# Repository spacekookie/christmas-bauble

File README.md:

# Kookies Christmas Bauble
A jolly christmas decoration on a PCB. Hoo hoo hoo!

It uses a 555 timer and a shift register + two buttons to generate patterns that are then displayed on a ring of simple LED's on the outside. The perfect thing to hang off your christmas tree in the jolly season (I know I'm early...) :)

The design uses SMD components (except for the LED's that are throughhole). The original schematic and layout was done by Ashley Mills (https://github.com/staropram). **The board requires only one layer**! It can thus be made at home (if the apropriate tools for cutting the PCB are present).

Check out my blog article [here](http://spacekookie.de/hardware/jolly-christmas-decoration/) for details :)
The christmas bauble went into production on 17.11.2015. Unfortunately Revision 3.1 got produced, not the updated and much cooler Rev 3.2** :/ Check out the picture belo.wspi

**All the revision 3 boards up to and including Rev 3.2 have a flaw where the XOR gate (U1) will make the functionality useless!**
Do not solder it on. You have to bridge two pins to make it work. Revision 3.3 fixes the issue.

## Pictures

## Partlist

Battery Holder: http://www.mouser.de/ProductDetail/Keystone-Electronics/3012TR/?qs=sGAEpiMZZMtT9MhkajLHrixYIYDZwOfD%2fKquWGKQDng%3d

Resistors: http://www.mouser.de/Passive-Components/Resistors/SMD-Resistors-Chip-Resistors/_/N-7h7yu?P=1yzmno7Z1yzmotu

595 Shift register: http://www.mouser.de/ProductDetail/Texas-Instruments/SN74HC165DR/?qs=sGAEpiMZZMtYFXwiBRPs00UWwMKcYyCs

555 Timer: http://www.mouser.de/ProductDetail/Texas-Instruments/TLC555CDR/?qs=sGAEpiMZZMuHTYi1bHPYELMHAyKcqQNZ

Capacitor: http://www.mouser.de/ProductDetail/Murata-Electronics/GRM32ER71E226KE15L/?qs=sGAEpiMZZMs0AnBnWHyRQAqZuYDIKiCDcXG6%252bp%252b0hpI%3d (you want 22 µF - Not sure if that's included in the Schematic and I'm too lazy to check right now)

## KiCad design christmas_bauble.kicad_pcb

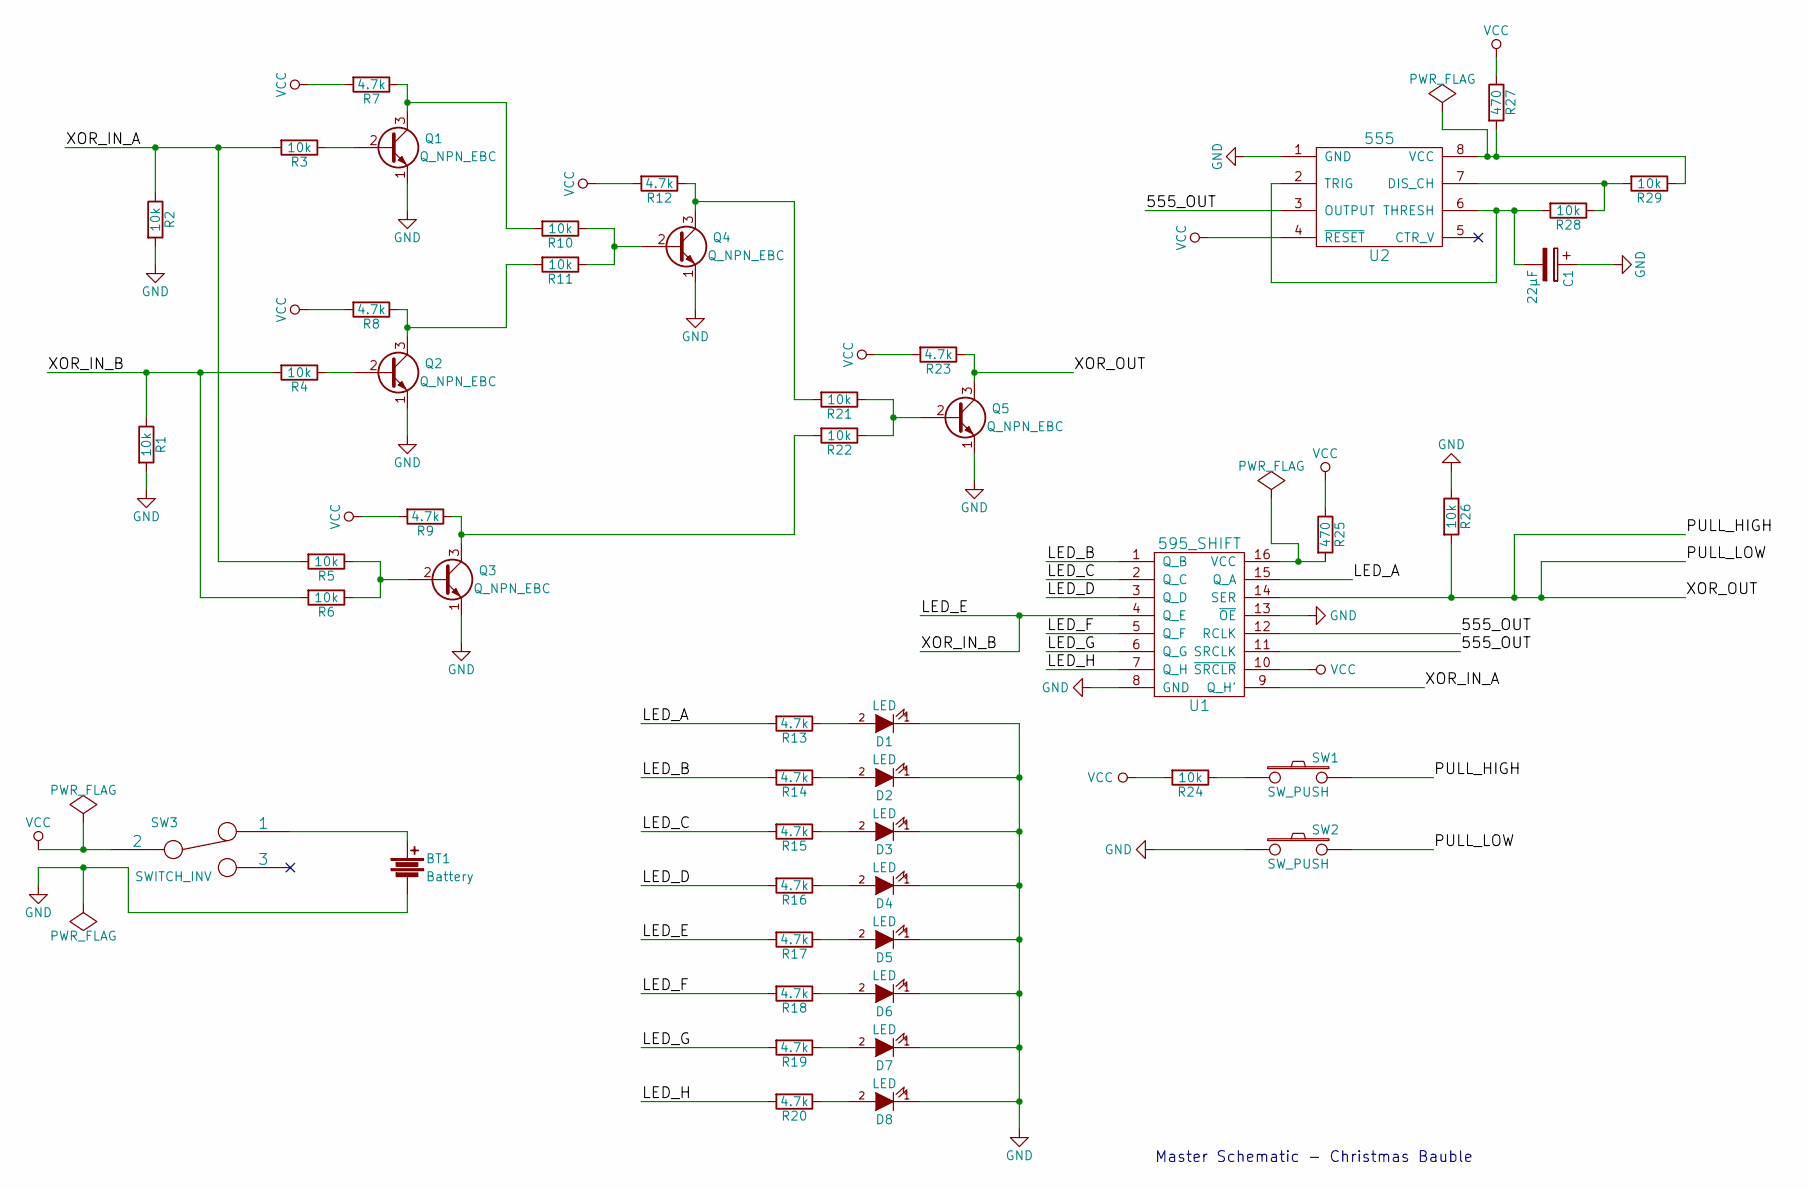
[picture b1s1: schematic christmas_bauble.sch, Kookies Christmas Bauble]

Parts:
BT1: Battery; COIN_BAT_HOLDER
C1: 22µF; C_2225_HandSoldering
D1, D2, D3, D4, D5, D6, D7, D8: LED; LED-5MM
Q1, Q2, Q3, Q4, Q5: Q_NPN_EBC; SOT-23_Handsoldering
R1, R2, R3, R4, R5, R6, R10, R11, R21, R22, R24, R26, R28, R29: 10k; R_1210_HandSoldering
R7, R8, R9, R12, R13, R14, R15, R16, R17, R18, R19, R20, R23: 4.7k; R_1210_HandSoldering
R25, R27: 470; R_1210_HandSoldering
SW1, SW2: SW_PUSH; SW_TACTILE_SHALLOW
SW3: SWITCH_INV; C1-1
U1: 595_SHIFT; SO-16-N
U2: 555; DIP-8_SMD

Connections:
/555_OUT: U1.11 (SRCLK), U1.12 (RCLK), U2.3 (OUTPUT)
/LED_A: R13.2, U1.15 (Q_A)
/LED_B: R14.2, U1.1 (Q_B)
/LED_C: R15.2, U1.2 (Q_C)
/LED_D: R16.2, U1.3 (Q_D)
/LED_E: R1.1, R4.2, R6.2, R17.2, U1.4 (Q_E)
/LED_F: R18.2, U1.5 (Q_F)
/LED_G: R19.2, U1.6 (Q_G)
/LED_H: R20.2, U1.7 (Q_H)
/PULL_HIGH: Q5.3 (C), R23.1, R26.2, SW1.2, SW2.2, U1.14 (SER)
/XOR_IN_A: R2.1, R3.2, R5.2, U1.9 (Q_H')
GND: BT1.2, C1.1, D1.1 (K), D2.1 (K), D3.1 (K), D4.1 (K), D5.1 (K), D6.1 (K), D7.1 (K), D8.1 (K), Q1.1 (E), Q2.1 (E), Q3.1 (E), Q4.1 (E), Q5.1 (E), R1.2, R2.2, R26.1, SW2.1, U1.8 (GND), U1.13 (~OE), U2.1 (GND)
unnamed: BT1.1, SW3.1
unnamed: C1.2, R28.2, U2.2 (TRIG), U2.6 (THRESH)
unnamed: D1.2 (A), R13.1
unnamed: D2.2 (A), R14.1
unnamed: D3.2 (A), R15.1
unnamed: D4.2 (A), R16.1
unnamed: D5.2 (A), R17.1
unnamed: D6.2 (A), R18.1
unnamed: D7.2 (A), R19.1
unnamed: D8.2 (A), R20.1
unnamed: Q1.2 (B), R3.1
unnamed: Q1.3 (C), R7.1, R10.2
unnamed: Q2.2 (B), R4.1
unnamed: Q2.3 (C), R8.1, R11.2
unnamed: Q3.2 (B), R5.1, R6.1
unnamed: Q3.3 (C), R9.1, R22.2
unnamed: Q4.2 (B), R10.1, R11.1
unnamed: Q4.3 (C), R12.1, R21.2
unnamed: Q5.2 (B), R21.1, R22.1
unnamed: R24.1, SW1.1
unnamed: R25.2, U1.16 (VCC)
unnamed: R27.2, R29.1, U2.8 (VCC)
unnamed: R28.1, R29.2, U2.7 (DIS_CH)
VCC: R7.2, R8.2, R9.2, R12.2, R23.2, R24.2, R25.1, R27.1, SW3.2, U1.10 (~SRCLR), U2.4 (~RESET)

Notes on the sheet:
Master Schematic - Christmas Bauble

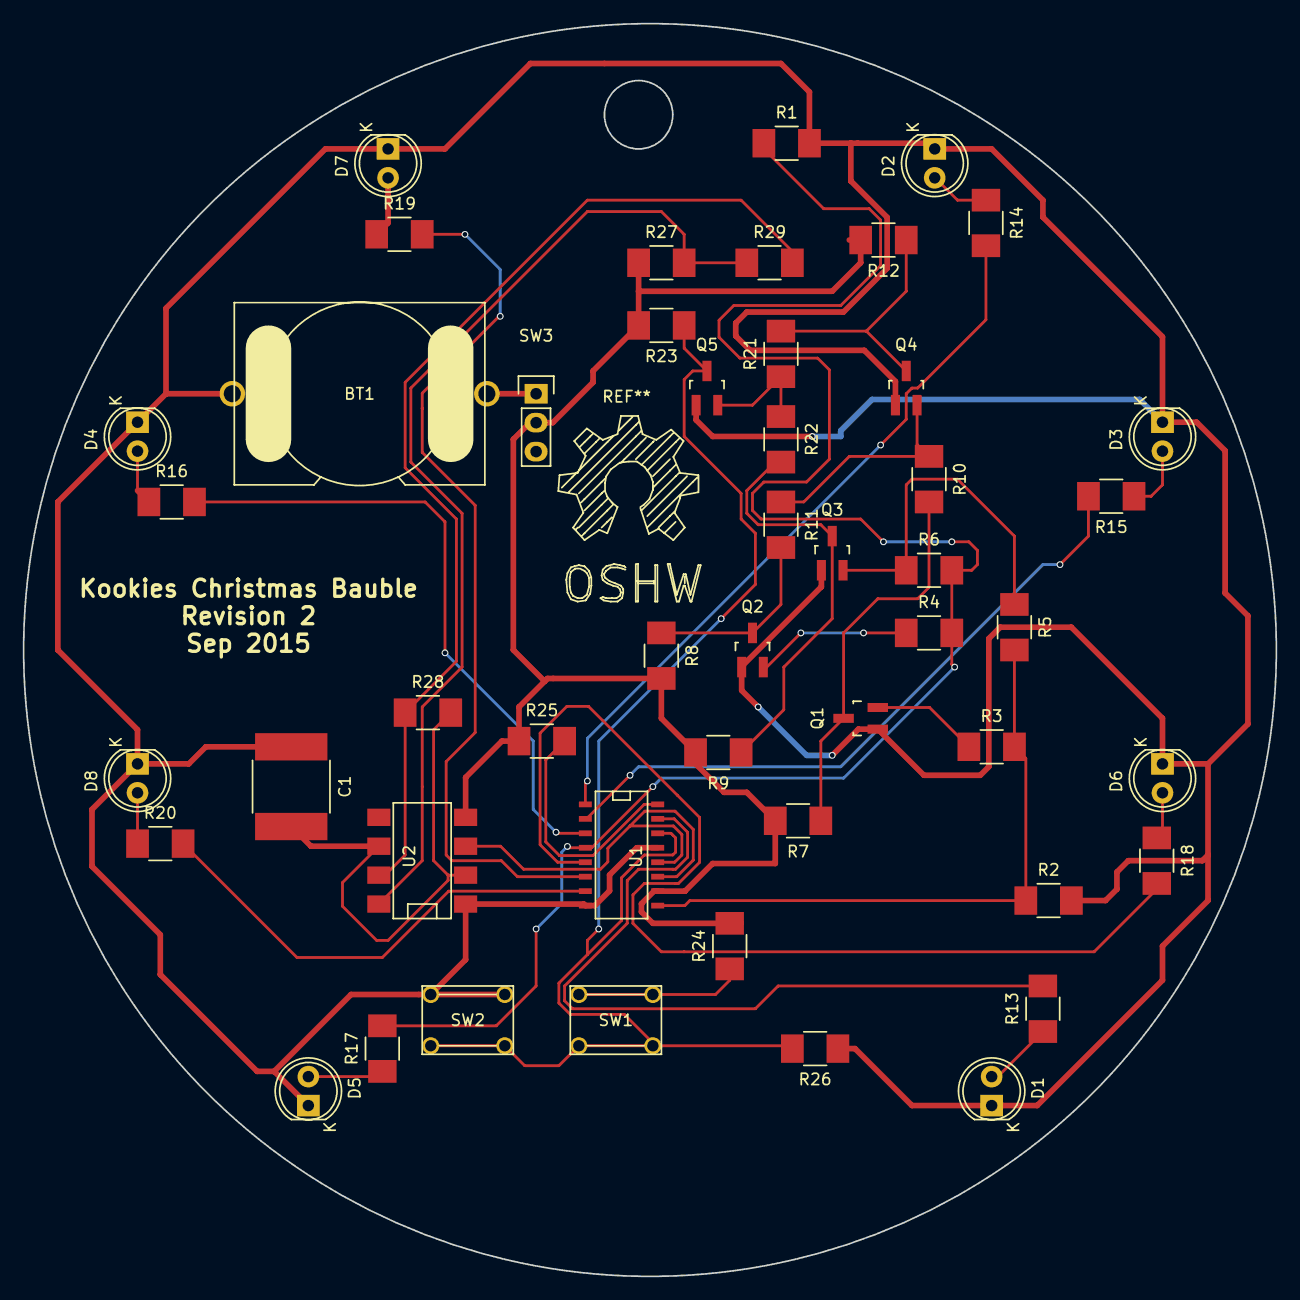
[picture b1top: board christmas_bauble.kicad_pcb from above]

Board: 2 copper layers, 110.0 x 110.0 mm, 49 parts (0 on the bottom side), 36 nets.

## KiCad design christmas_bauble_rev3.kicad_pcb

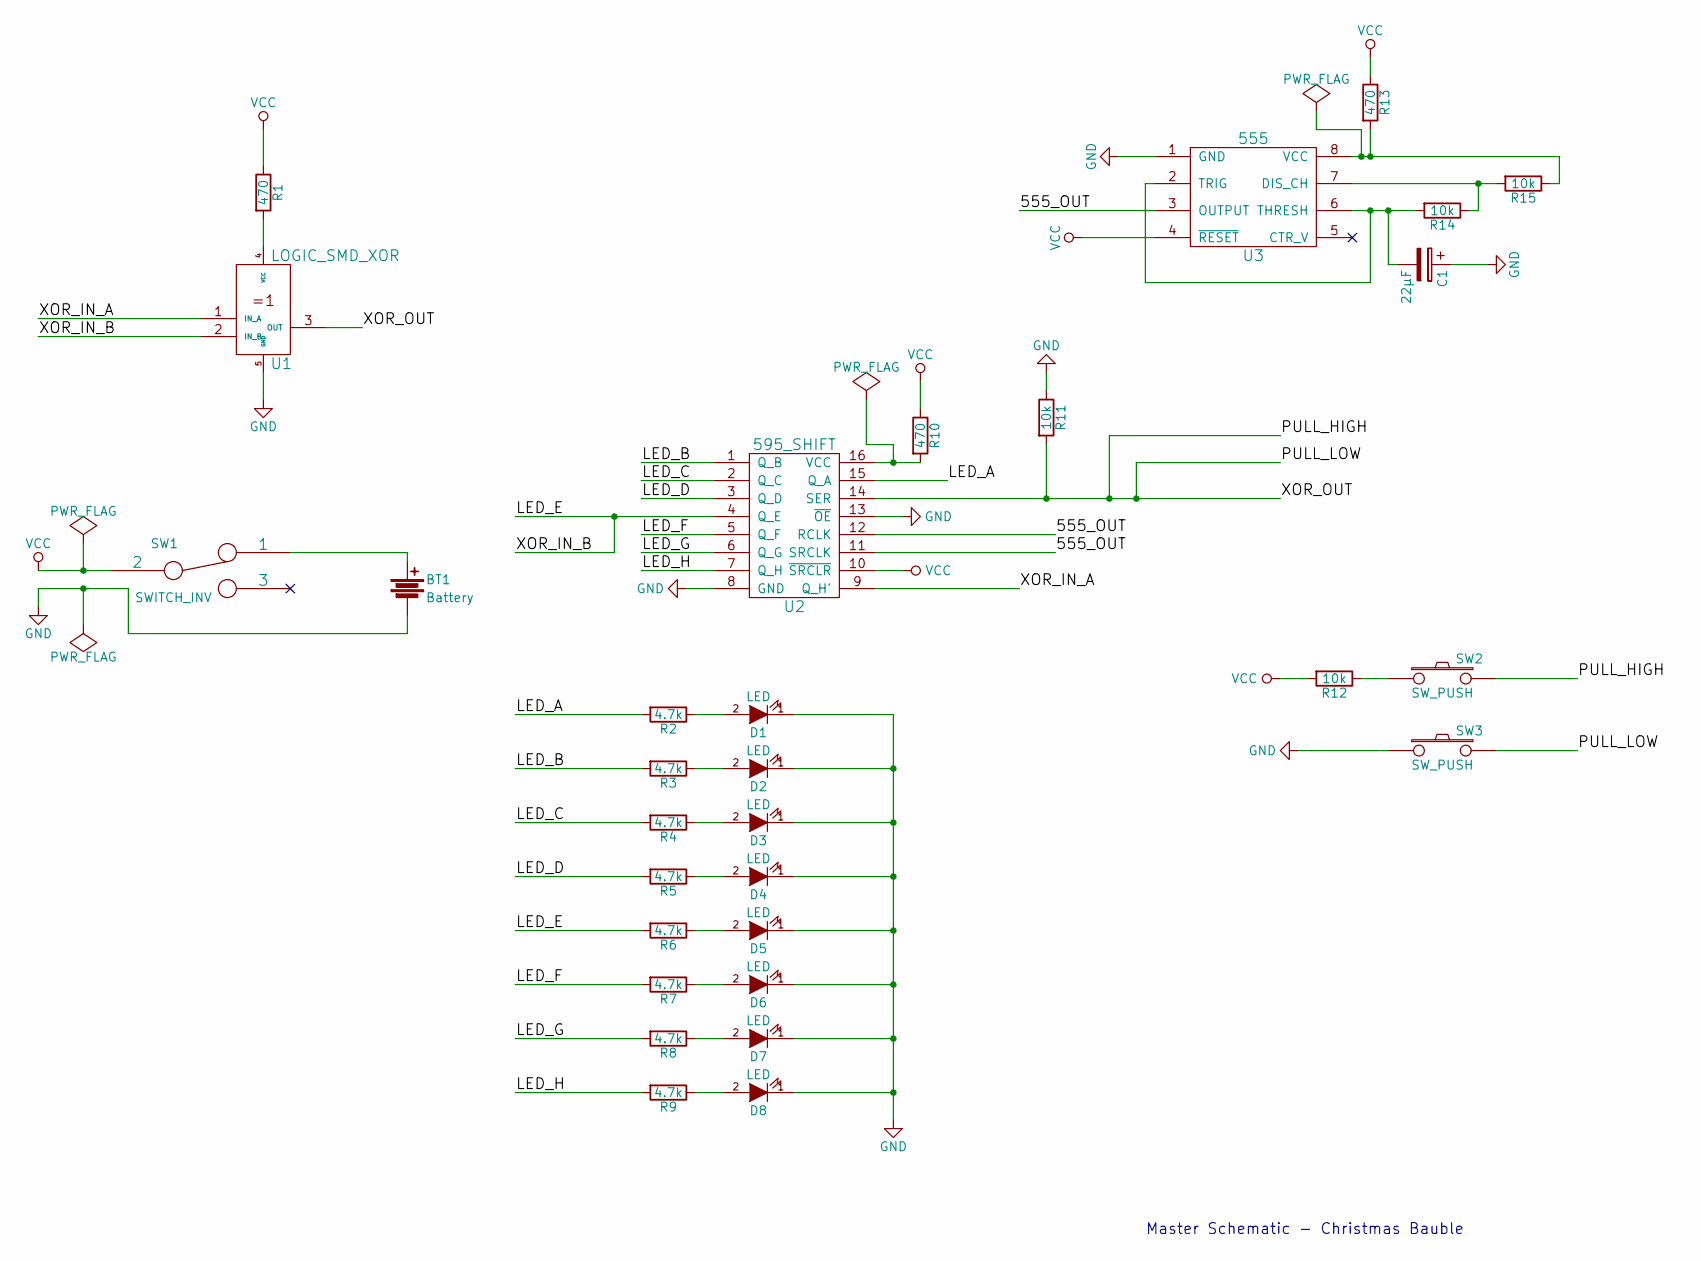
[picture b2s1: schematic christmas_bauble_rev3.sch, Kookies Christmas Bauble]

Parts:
BT1: Battery; COIN_BAT_HOLDER
C1: 22µF; C_2225_HandSoldering
D1, D2, D3, D4, D5, D6, D7, D8: LED; LED-5MM
R1, R10, R13: 470; R_0805_HandSoldering
R2, R3, R4, R5, R6, R7, R8, R9: 4.7k; R_0805_HandSoldering
R11, R12, R14, R15: 10k; R_0805_HandSoldering
SW1: SWITCH_INV; C1-1
SW2, SW3: SW_PUSH; SW_TACTILE_SHALLOW
U1: LOGIC_SMD_XOR; LOGIC_SMD_5PIN_SOT-23-5
U2: 595_SHIFT; SO-16-N
U3: 555; DIP-8_SMD

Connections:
/555_OUT: U2.11 (SRCLK), U2.12 (RCLK), U3.3 (OUTPUT)
/LED_A: R2.2, U2.15 (Q_A)
/LED_B: R3.2, U2.1 (Q_B)
/LED_C: R4.2, U2.2 (Q_C)
/LED_D: R5.2, U2.3 (Q_D)
/LED_E: R6.2, U1.2 (IN_B), U2.4 (Q_E)
/LED_F: R7.2, U2.5 (Q_F)
/LED_G: R8.2, U2.6 (Q_G)
/LED_H: R9.2, U2.7 (Q_H)
/PULL_HIGH: R11.2, SW2.2, SW3.2, U1.3 (OUT), U2.14 (SER)
/XOR_IN_A: U1.1 (IN_A), U2.9 (Q_H')
GND: BT1.2, C1.1, D1.1 (K), D2.1 (K), D3.1 (K), D4.1 (K), D5.1 (K), D6.1 (K), D7.1 (K), D8.1 (K), R11.1, SW3.1, U1.5 (GND), U2.8 (GND), U2.13 (~OE), U3.1 (GND)
unnamed: BT1.1, SW1.1
unnamed: C1.2, R14.2, U3.2 (TRIG), U3.6 (THRESH)
unnamed: D1.2 (A), R2.1
unnamed: D2.2 (A), R3.1
unnamed: D3.2 (A), R4.1
unnamed: D4.2 (A), R5.1
unnamed: D5.2 (A), R6.1
unnamed: D6.2 (A), R7.1
unnamed: D7.2 (A), R8.1
unnamed: D8.2 (A), R9.1
unnamed: R1.2, U1.4 (VCC)
unnamed: R10.2, U2.16 (VCC)
unnamed: R12.1, SW2.1
unnamed: R13.2, R15.1, U3.8 (VCC)
unnamed: R14.1, R15.2, U3.7 (DIS_CH)
VCC: R1.1, R10.1, R12.2, R13.1, SW1.2, U2.10 (~SRCLR), U3.4 (~RESET)

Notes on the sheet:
Master Schematic - Christmas Bauble

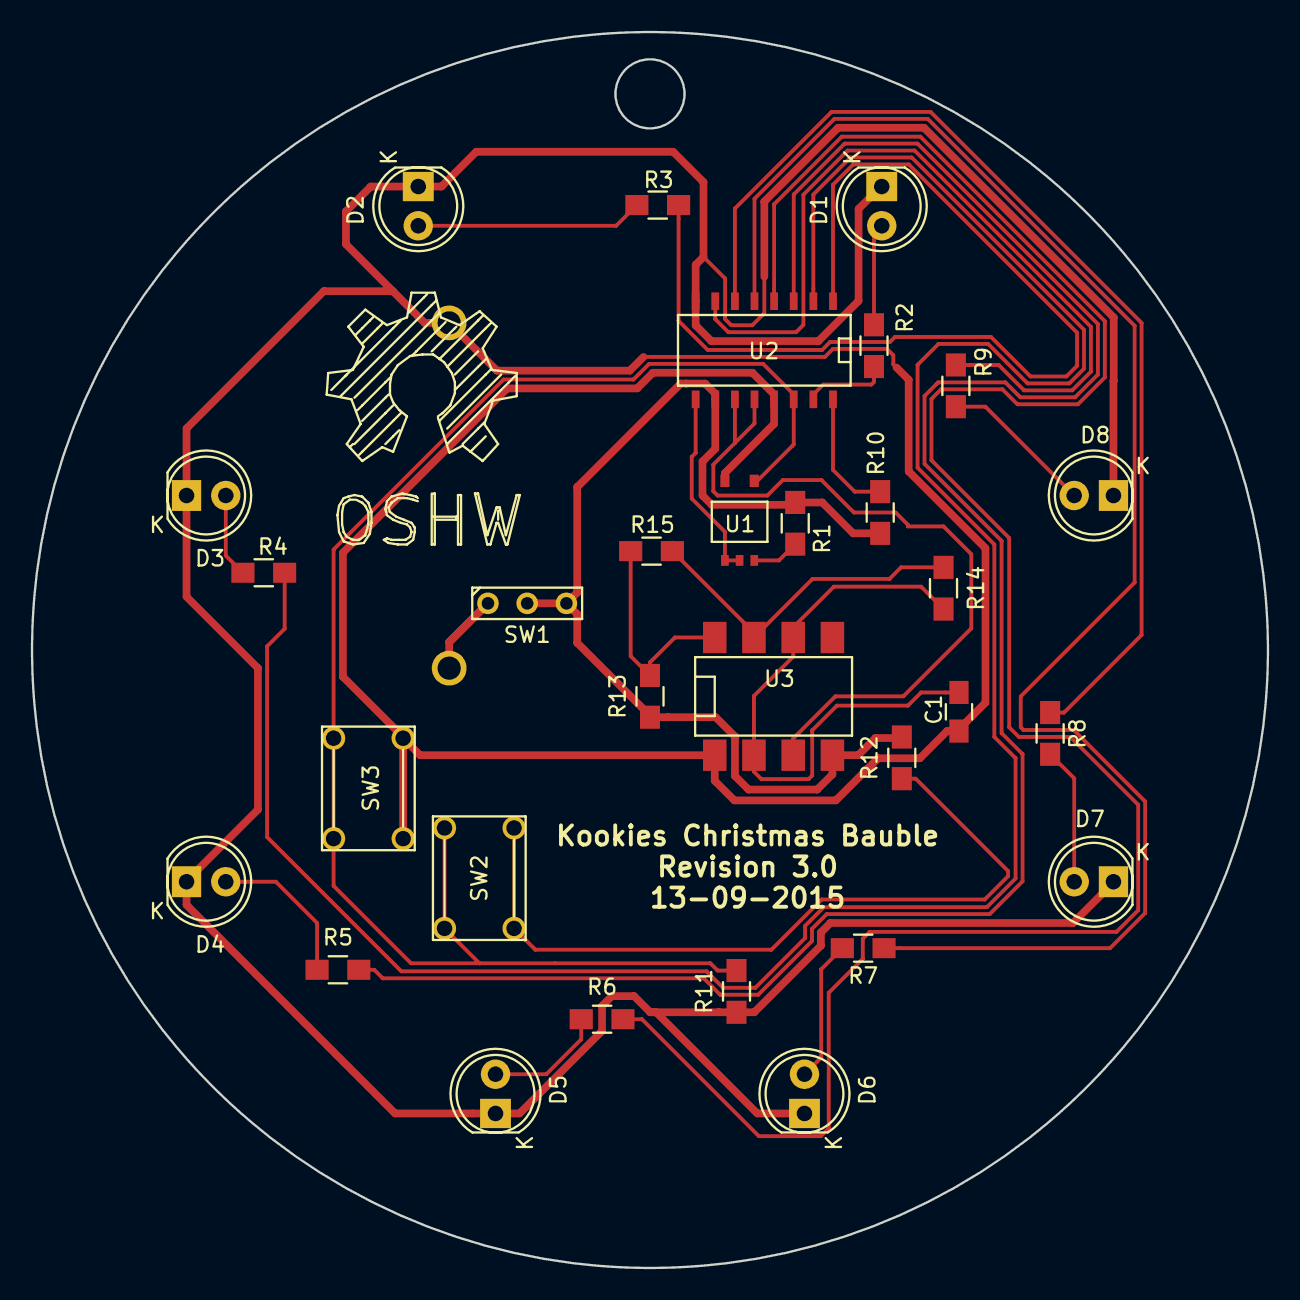
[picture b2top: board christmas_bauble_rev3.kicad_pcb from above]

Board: 2 copper layers, 80.0 x 80.0 mm, 32 parts (1 on the bottom side), 28 nets.

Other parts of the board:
SYM: Symbol_OSHW-Logo_SilkScreen_BIG

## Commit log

2015-09-12 Adding first and second revision schematics and pcb.
2015-09-12 Updating the README a bit.
2015-09-12 Updating stuff
2015-09-12 Updating README picture links
2015-09-13 Finishing Revision 3 PCB which uses a single SMD XOR gate instead of one built from NPN transistors which greatly riduces the amount of traces required. Now only using one layer!
2015-09-13 Changing pictures on the README
2015-11-13 Some minor changes. This is the version that went into production. Woop woop \o/
2015-11-17 Changing batteries on the board to 2 20mm coin cell batteries in paralell for longer lifetime. Routing batteries on the back via SMD holders.
2015-11-17 Updating README a litle
2015-11-26 Adding new picture and cleaning up repo. Old revisions are now archived.
2016-01-01 Adding skeleton for revision 4 bauble...
2016-01-05 Adding dip switches to the layout to program the bauble
2016-01-05 Adding more debugging LEDs and a switch for 'Programmer mode'
2016-03-20 Updating some revision 4 files.
